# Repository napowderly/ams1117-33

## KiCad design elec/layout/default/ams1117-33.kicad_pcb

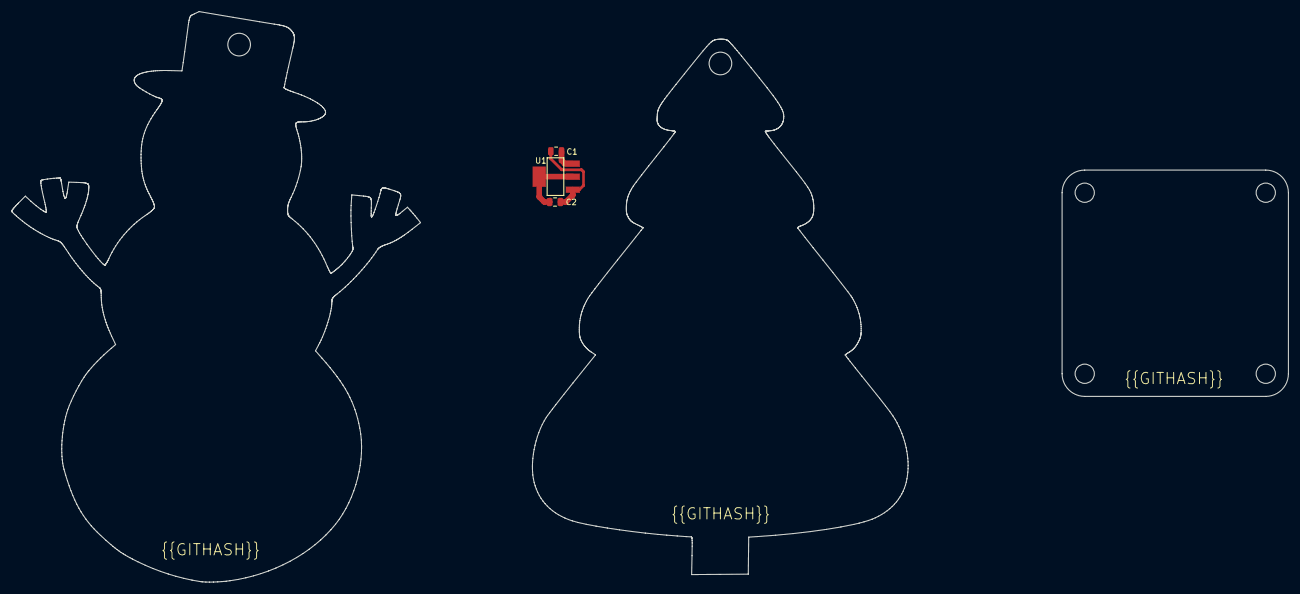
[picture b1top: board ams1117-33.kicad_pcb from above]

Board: 2 copper layers, 66.4 x 94.6 mm, 3 parts (0 on the bottom side), 3 nets.

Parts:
C1, C2: Multilayer Ceramic Capacitors MLCC - SMD/SMT 10uF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; C0805
U1: SOT-223-3_L6.5-W3.4-P2.30-LS7.0-BR

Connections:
gnd: C1.2, C2.2, U1.1
vcc: C1.1, U1.3
vcc-1: C2.1, U1.2, U1.4

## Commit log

2024-02-16 Configure project
2024-02-16 initial design:
2024-02-16 layout
2024-03-08 update layout
